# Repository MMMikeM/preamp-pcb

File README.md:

# route6
Step-by-step 6-layer routing helpers for the humbucker preamp board. Start with `REVIEW.md`.

    pip install -r requirements.txt
    python -m pytest -q tests                 # about 2 minutes
    python via_justify.py tests/board_4layer_rev1.kicad_pcb
    python stage_route.py setup --from ../../../humbucker-preamp.kicad_pcb
    python stage_route.py 2b                  # then 2c; steps 2a, 2p, 2d, 2e, 2i, 2f also need ROUTER_DIR
    python stage_route.py check --final       # also fails on unconnected nets, unjustified vias (P1-P3), copper that joins nothing
                                              # and nets too long off the top layer; --board PATH checks that board instead

    python score.py work/2i.kicad_pcb OTHER.kicad_pcb --classes work/net_classes.json   # weighted score, and what changed and why

Everything is written to `work/`. The project board is only read.

## Steps
`setup -> 2a -> 2p -> 2b -> 2c -> 2d -> 2e -> 2h -> 2i -> 2f -> check`. Each step saves `work/<step>.kicad_pcb` and
`work/<step>_checks.json`, and exits 1 if a script or the router it runs fails, or if a must-fix check is not empty.
A step that exits 1 puts `work/board.kicad_pcb` back to what it was before the step, so it can be rerun; the result that
failed stays in `work/<step>.kicad_pcb` to look at. A board with arc tracks is refused: straighten them in KiCad first.

- `setup` also sets the board's via defaults to filled and capped, because the drops put vias in pads, and saves the net
  classes from the `.kicad_pro` beside the board to `work/net_classes.json`. A ground pad set to no zone connection (J105,
  J205: no room for spokes) gets a top-layer link to the nearest ground pad, since the pours do not reach it.
- `2p` routes the front-end (P2_FrontEnd) and second-stage (P4_Stage2) nets on the top layer with no vias, before `2b`'s
  links can take their way: drains first, then the second stage, then the rest of the front end, a router call each. A net
  is kept only if it joins and passes 2e's pass-1 judging; the rest is left for `2e`.
- `2d` adds no top-layer supply links of its own: `2b` has already joined supply pads up to 4 mm apart. It drops the supply
  vias, then lays one V+ and one V- zone on L5 from the router's split plane (`route_planes.py`, the "spine split"): GND
  stays the layer's background, and each rail's zone is grown round its own pads and vias and joined by corridors laid so
  the two never cross. Nothing is placed by coordinates. The battery and bias nets are routed after the zones, and
  `zone_integrity` fails the step if one cuts a zone. A rail pad the zone misses gets an L3 hop to its own zone, and 2d
  fails if V+ or V- is still open. `R6_SKIP_SUPPLY=1` leaves the zones out, for comparing signal
  routing between placements. `via_justify.py` judges V+, V- and the bias nets by 2b's limits.
- `2a`, `2p`, `2b` and `2e` leave alone only the nets `2h` will copy, and route everything else on both channels. `2h` then
  copies those nets, skipping any whose copy would collide with copper that is staying, and `2i` routes whatever the copy
  did not cover. When no net has a twin (channels laid out by hand), `2h` copies nothing and passes.
- `2e` and `2i` fail on a net left open. A net off the top layer longer than max(1.8 x its tree, tree + 12 mm) (P4 and P5
  nets, being low-impedance, get 2.2 x) does not stop the run: `check --final` reports it (a warning on P4/P5), so the
  placement can be judged on a whole board. Both remove the vias and tracks that end up joining nothing (a pad via whose L3
  join was made another way, a track stub with a free end); `2d` does the same for the battery and bias vias. A V+ or V-
  via its zone misses is left for `check --final` to report. A pair the via check flags is routed again on top, with only
  the inner-layer track between the two pieces lifted. A net still open, or a front-end net joined off the top layer at
  over 1.5 x its tree, with L3 track of a lower-priority signal or bias net in its way, is joined again with those tracks
  lifted and they are routed again round it: once lifting the bias alone, once every lower-priority net in the way. Of the
  results where it joins and nothing is left open, squeezed or cut, the one with the lowest routing score (`score.py`) is
  kept, if the net was open or the score drops.
- With the net classes from setup, an unjustified via is must-fix on P1-P3, a warning on P4-P6 and not reported on any
  other net (power, battery and ground are low-impedance, so a via costs nothing there).
- `2f` puts a via in each loose test point where one fits and has the router reach the rest by a track, then clears
  anything left joining nothing on every net but the rails and ground.

## The router (KiCadRoutingTools)
Set `ROUTER_DIR` to a checkout of https://github.com/drandyhaas/KiCadRoutingTools (MIT). It does two jobs here:

1. Steps 2a, 2p, 2d, 2e, 2i and 2f call its `py_router/route.py`, and 2d also its `py_router/route_planes.py`. That needs its compiled extension (`python build_router.py` there).
2. With `ROUTER_DIR` set, every step also gets a second opinion from its DRC and connectivity check (`krt_checks.py`).
   This part needs only `scipy` and `Pillow`, not the compiled extension. Its DRC items are must-fix. Nets that only it
   calls unconnected are listed as `krt_unconnected_extra` and are for a human to settle in KiCad after refilling zones.
   Without KiCad's own refill (`KICAD_PYTHON`) the router estimates a pour's fill, and that estimate misses vias on a zone's
   edge that KiCad's fill reaches; so a zoned net whose every pad reaches its zone through copper by route6's count is
   listed apart, as `krt_zone_fill_only`, and left to KiCad's DRC.

Without `ROUTER_DIR` the second opinion is skipped and the step says so.

What route6 keeps for itself, because the router has no equivalent: the unjustified-via check, short same-net links
before general routing (the router joins a net's short gaps last), via-in-pad drops by rule, copying one channel to the
other, and the 4-to-6-layer conversion. `board.py` stays because the router's writer cannot remove a track by uuid or
leave the rest of the file untouched.

## Known open items
- A full run on that placement ends with every step clean but 8 nets not fully connected and 4 unjustified vias, so
  `check --final` exits 1. `REVIEW.md` weak spot 1 lists them. A full run takes about ten minutes.

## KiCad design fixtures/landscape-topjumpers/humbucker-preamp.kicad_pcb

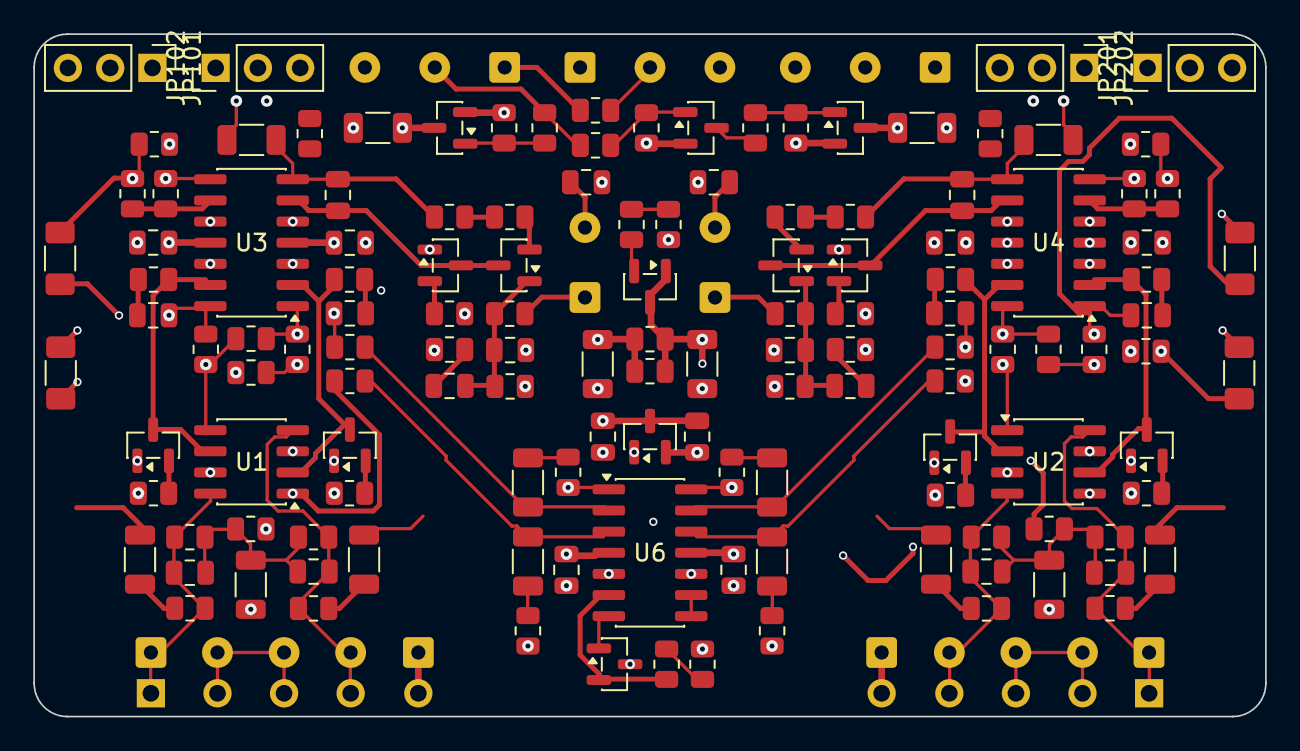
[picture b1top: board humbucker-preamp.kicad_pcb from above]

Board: 6 copper layers, 74.0 x 41.0 mm, 147 parts (0 on the bottom side), 93 nets.

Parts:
C101, C102, C201, C202: 220p; C_0805_2012Metric
C103, C104, C105, C113, C114, C203, C204, C205, C213, C214, C305, C306: 100n; C_1206_3216Metric
C106, C107, C111, C206, C207, C211: 270p; C_0805_2012Metric
C108, C208: 12n; C_0805_2012Metric
C109, C209: 3.3n; C_0805_2012Metric
C110, C210, C303, C304, C307, C308, C309, C310, C311, C312: 1u; C_0805_2012Metric
C112, C212, C301, C302: 47u; C_1206_3216Metric
J1: Battery (+ 0 -); SolderWire-0.25sqmm_1x03_P4.2mm_D0.65mm_OD1.7mm
J2: Blend pot 10k lin; SolderWire-0.25sqmm_1x03_P4.2mm_D0.65mm_OD1.7mm
J3: Output jack (tip, ring, sleeve); SolderWire-0.25sqmm_1x03_P4.2mm_D0.65mm_OD1.7mm
J101, J201: Pickup; SolderWire-0.25sqmm_1x04_P4.0mm_D0.65mm_OD1.7mm
J102, J202: Aux (GA, LINK, LINK, GB); Holes_1x04_P4.00mm
J103, J203: HP pot 500k; SolderWire-0.25sqmm_1x02_P4.2mm_D0.65mm_OD1.7mm
J104, J204: Pickup GND; SolderWire-0.25sqmm_1x01_D0.65mm_OD1.7mm
J105, J205: Aux GND; Holes_1x01
JP101, JP201: DRIVE A; PinHeader_1x03_P2.54mm_Vertical
JP102, JP202: DRIVE B; PinHeader_1x03_P2.54mm_Vertical
Q101, Q102, Q104, Q201, Q202, Q204, Q301, Q304: BC860C; SOT-23
Q103, Q203, Q302, Q303, Q305: BC850C; SOT-23
R101, R102, R124, R126, R201, R202, R224, R226: 47M; R_0805_2012Metric
R103, R104, R127, R203, R204, R227, R302, R303, R310: 330k; R_0805_2012Metric
R105, R108, R111, R112, R116, R120, R205, R208, R211, R212, R216, R220, R313: 1k; R_0805_2012Metric
R106, R107, R113, R121, R206, R207, R213, R221: 2k; R_0805_2012Metric
R109, R110, R114, R115, R119, R209, R210, R214, R215, R219, R307, R308, R309, R312: 15k; R_0805_2012Metric
R117, R122, R217, R222, R305, R311: 47k; R_0805_2012Metric
R118, R218, R301, R304, R306: 2.2M; R_0805_2012Metric
R123, R125, R223, R225: 10M; R_0805_2012Metric
RS101, RS102, RS201, RS202: 5.6k; R_1206_3216Metric_Pad1.30x1.75mm_HandSolder
U1, U2: JFE2140; SOIC-8_3.9x4.9mm_P1.27mm
U3, U4: TLV9104; SOIC-14_3.9x8.7mm_P1.27mm
U5: REF3312; SOT-23
U6: TLV9144; SOIC-14_3.9x8.7mm_P1.27mm

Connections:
/BAT+: J1.1, Q301.2 (E), R301.1
/BAT-: J1.3, Q302.2 (E), Q303.2 (E), R304.2, R306.2
/Bridge/BO: C211.2, C212.1, R220.1, U4.8
/Bridge/CLD: JP201.3, JP202.3, R213.1, R214.1, RS202.2
/Bridge/DA: Q201.3 (C), R211.1, U2.2 (D1), U4.13 (-)
/Bridge/DB: Q202.3 (C), R212.1, U2.6 (D2), U4.2 (-)
/Bridge/DRVA: C204.1, JP201.2
/Bridge/DRVB: C205.2, JP202.2
/Bridge/GA: C201.1, J201.1, J202.1, R201.1, R203.2, U2.8 (G2)
/Bridge/GB: C202.2, J201.4, J202.4, R202.2, R204.1, U2.4 (G1)
/Bridge/LINK: J201.2, J201.3, J202.2, J202.3
/Bridge/OA: C206.2, R206.1, R207.2, R223.1, U4.14
/Bridge/OB: C207.2, R208.1, R216.1, RS202.1, U4.1
/Bridge/OBN: JP201.1, JP202.1, R215.2, U4.7
/Bridge/SA: R205.1, R206.2, R225.1, RS201.2, U2.1 (S1)
/Bridge/SB: R207.1, R208.2, RS201.1, U2.5 (S2)
/Bridge/SO: R224.2, R227.1, U6.14
/Bridge/SVN: C213.1, R223.2, U6.13 (-)
/Bridge/SVN_I: C213.2, R224.1
/Bridge/SVP: C214.1, R225.2, U6.12 (+)
/Bridge/SVP_I: C214.2, R226.1
/Bridge/VB: C201.2, C202.1, C203.1, R201.2, R202.1, R227.2
/Neck/BO: C111.2, C112.1, R120.1, U3.7
/Neck/CLD: JP101.3, JP102.3, R113.1, R114.1, RS102.2
/Neck/DA: Q101.3 (C), R111.1, U1.2 (D1), U3.2 (-)
/Neck/DB: Q102.3 (C), R112.1, U1.6 (D2), U3.13 (-)
/Neck/DRVA: C104.1, JP101.2
/Neck/DRVB: C105.2, JP102.2
/Neck/GA: C101.1, J101.1, J102.1, R101.1, R103.2, U1.8 (G2)
/Neck/GB: C102.2, J101.4, J102.4, R102.2, R104.1, U1.4 (G1)
/Neck/LINK: J101.2, J101.3, J102.2, J102.3
/Neck/OA: C106.2, R106.1, R107.2, R123.1, U3.1
/Neck/OB: C107.2, R108.1, R116.1, RS102.1, U3.14
/Neck/OBN: JP101.1, JP102.1, R115.2, U3.8
/Neck/SA: R105.1, R106.2, R125.1, RS101.2, U1.1 (S1)
/Neck/SB: R107.1, R108.2, RS101.1, U1.5 (S2)
/Neck/SO: R124.2, R127.1, U6.1
/Neck/SVN: C113.1, R123.2, U6.2 (-)
/Neck/SVN_I: C113.2, R124.1
/Neck/SVP: C114.1, R125.2, U6.3 (+)
/Neck/SVP_I: C114.2, R126.1
/Neck/VB: C101.2, C102.1, C103.1, R101.2, R102.1, R127.2
/OUT_BR: C212.2, J2.3, R222.1
/OUT_NK: C112.2, J2.1, R122.1
/RING: J3.2, R303.1, R305.1
/TIP: J3.1, R313.2
/VR: C303.1, U5.2 (OUT), U6.5 (+)
GND: C103.2, C109.2, C110.2, C203.2, C209.2, C210.2, C301.2, C302.1, C304.1, C307.2, C308.1, C309.2, C310.1, C311.2, C312.1, J1.2, J3.3, J104.1 (Pin_1_1), J105.1 (Pin_1_1), J204.1 (Pin_1_1), J205.1 (Pin_1_1), R105.2, R113.2, R118.2, R122.2, R126.2, R205.2, R213.2, R218.2, R222.2, R226.2, U3.10 (+), U4.5 (+), U5.1 (IN), U6.10 (+)
unnamed: C104.2, R103.1
unnamed: C105.1, R104.2
unnamed: C106.1, R111.2
unnamed: C107.1, R112.2
unnamed: C108.1, R116.2
unnamed: C204.2, R203.1
unnamed: C205.1, R204.2
unnamed: C206.1, R211.2
unnamed: C207.1, R212.2
unnamed: C208.1, R216.2
unnamed: J2.2, R313.1
unnamed: J103.1, R117.2
unnamed: C110.1, J103.2
unnamed: J203.1, R217.2
unnamed: C210.1, J203.2
unnamed: Q101.2 (E), R109.2
unnamed: Q102.2 (E), R110.2
unnamed: C108.2, C109.1, Q103.1 (B), R117.1, R118.1
unnamed: C111.1, Q103.3 (C), Q104.3 (C), U3.6 (-)
unnamed: Q103.2 (E), R121.2
unnamed: Q104.2 (E), R119.2
unnamed: Q201.2 (E), R209.2
unnamed: Q202.2 (E), R210.2
unnamed: C208.2, C209.1, Q203.1 (B), R217.1, R218.1
unnamed: C211.1, Q203.3 (C), Q204.3 (C), U4.9 (-)
unnamed: Q203.2 (E), R221.2
unnamed: Q204.2 (E), R219.2
unnamed: Q301.1 (B), R301.2, R302.1
unnamed: Q302.1 (B), R303.2, R304.1
unnamed: Q302.3 (C), R302.2
unnamed: Q303.1 (B), R305.2, R306.1
unnamed: Q304.2 (E), R308.2
unnamed: Q305.1 (B), U6.7
unnamed: Q305.2 (E), R311.1, U6.6 (-)
unnamed: R120.2, R121.1
unnamed: R220.2, R221.1
unnamed: R307.2, R308.1
unnamed: R311.2, R312.1
unnamed: R114.2, R115.1, U3.9 (-)
unnamed: R214.2, R215.1, U4.6 (-)
unnamed: U6.8, U6.9 (-)
PB: C305.2, Q101.1 (B), Q102.1 (B), Q104.1 (B), Q201.1 (B), Q202.1 (B), Q204.1 (B), Q304.1 (B), Q304.3 (C), R309.1, R310.1
REF: C306.2, Q305.3 (C), R309.2, R310.2, U3.3 (+), U3.5 (+), U3.12 (+), U4.3 (+), U4.10 (+), U4.12 (+)
V+: C301.1, C305.1, C306.1, C307.1, C309.1, C311.1, Q301.3 (C), R109.1, R110.1, R119.1, R209.1, R210.1, R219.1, R307.1, U1.3 (VCH), U2.3 (VCH), U3.4 (V+), U4.4 (V+), U6.4 (V+)
V-: C302.2, C303.2, C304.2, C308.2, C310.2, C312.2, Q303.3 (C), R312.2, U1.7 (VCL), U2.7 (VCL), U3.11 (V-), U4.11 (V-), U5.3 (COM), U6.11 (V-)
